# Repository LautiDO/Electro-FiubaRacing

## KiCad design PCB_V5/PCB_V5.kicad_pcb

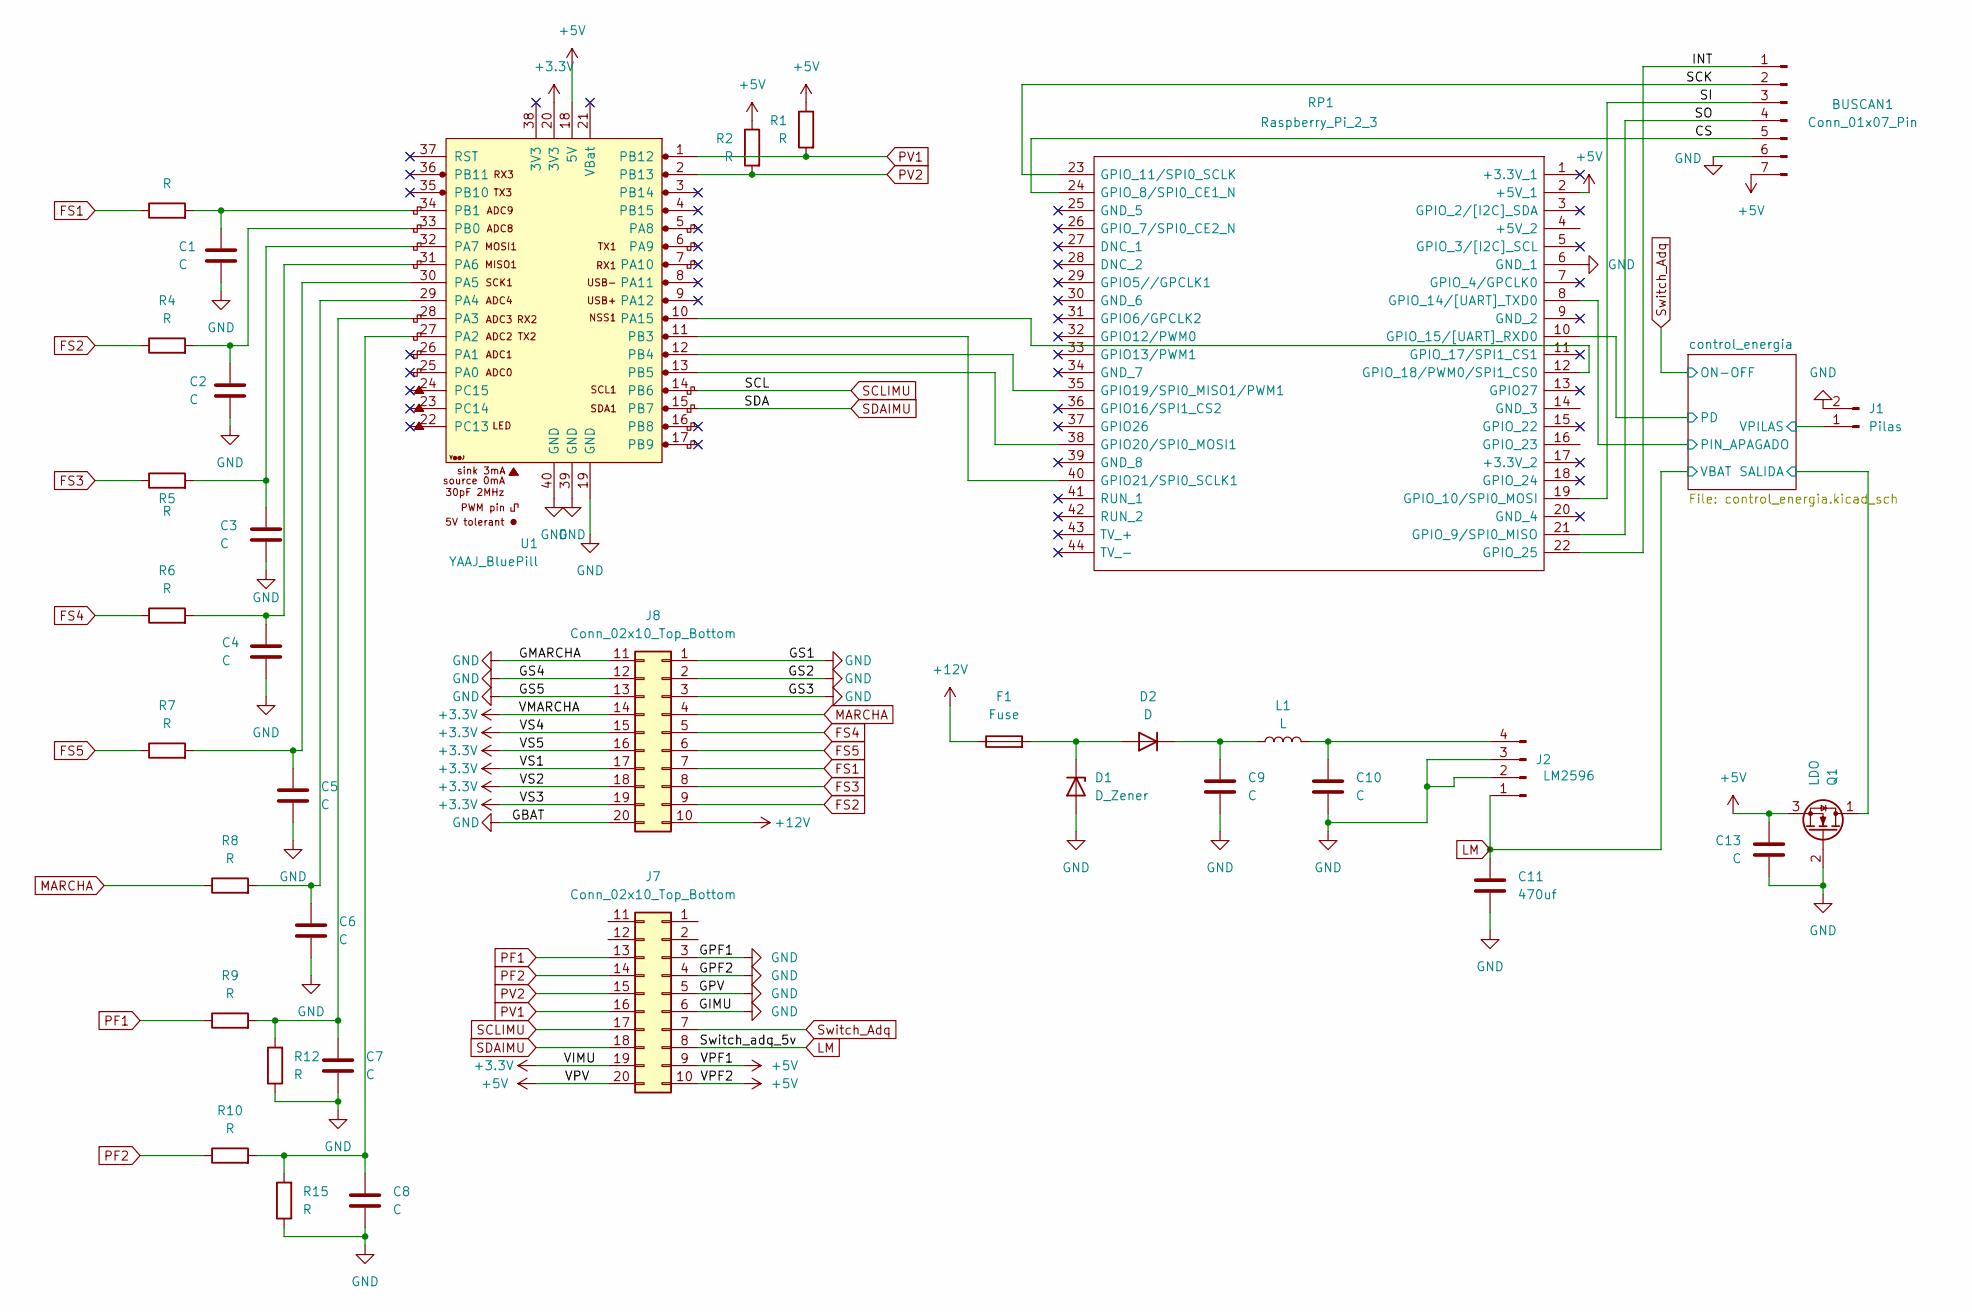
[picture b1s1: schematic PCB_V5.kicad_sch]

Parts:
BUSCAN1: Conn_01x07_Pin; PinHeader_1x07_P2.54mm_Vertical
C1, C2, C3, C4, C5, C6, C7, C8, C9, C10, C13: C; CP_Radial_D5.0mm_P2.50mm
C11: 470uf; CP_Radial_D5.0mm_P2.50mm
D1: D_Zener; D_DO-201_P15.24mm_Horizontal
D2: D; D_DO-201_P15.24mm_Horizontal
F1: Fuse; Fuseholder_Cylinder-5x20mm_Schurter_0031_8201_Horizontal_Op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
J1: Pilas; TerminalBlock_Phoenix_PT-1,5-2-5.0-H_1x02_P5.00mm_Horizontal
J2: LM2596; PinHeader_1x04_P2.54mm_Vertical
J7, J8: Conn_02x10_Top_Bottom; Molex_Mini-Fit_Jr_5566-20A2_2x10_P4.20mm_Vertical
L1: L; Transformer_CHK_EI38-3VA_Neutral
Q1: LDO; TO-220-3_Vertical
R1, R2, R3, R4, R5, R6, R7, R8, R9, R10, R12, R15: R; R_Axial_DIN0207_L6.3mm_D2.5mm_P7.62mm_Horizontal
RP1: Raspberry_Pi_2_3; PinHeader_2x20_P2.54mm_Vertical; Manufacturer_Part_Number Raspberry Pi 2 or 3
U1: YAAJ_BluePill; PinHeader_2x20_P2.54mm_Vertical

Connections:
+3.3V: J7.19, J8.14, J8.15, J8.16, J8.17, J8.18, J8.19, U1.20 (3V3)
+5V: BUSCAN1.7, C13.1, J7.9, J7.10, J7.20, Q1.3 (S), R1.1, R2.1, RP1.2 (+5V_1), U1.18 (5V)
+12V: F1.1, J8.10
/CS: BUSCAN1.5, RP1.24 (GPIO_8/SPI0_CE1_N)
/INT: BUSCAN1.1, RP1.22 (GPIO_25)
/SCK: BUSCAN1.2, RP1.23 (GPIO_11/SPI0_SCLK)
/SI: BUSCAN1.3, RP1.19 (GPIO_10/SPI0_MOSI)
/SO: BUSCAN1.4, RP1.21 (GPIO_9/SPI0_MISO)
/control_energia/PD: RP1.10 (GPIO_15/[UART]_RXD0); also elsewhere on the board
/control_energia/PIN_APAGADO: RP1.8 (GPIO_14/[UART]_TXD0); also elsewhere on the board
/control_energia/SALIDA: Q1.1 (D); also elsewhere on the board
/control_energia/VPILAS: J1.1; also elsewhere on the board
FS1: J8.7, R3.1
FS2: J8.9, R4.1
FS3: J8.8, R5.1
FS4: J8.5, R6.1
FS5: J8.6, R7.1
GND: BUSCAN1.6, C1.2, C2.2, C3.2, C4.2, C5.2, C6.2, C7.2, C8.2, C9.2, C10.2, C11.2, C13.2, D1.2 (A), J1.2, J2.2, J2.3, J7.3, J7.4, J7.5, J7.6, J8.1, J8.2, J8.3, J8.11, J8.12, J8.13, J8.20, Q1.2 (G), R12.1, R15.1, RP1.6 (GND_1), U1.19 (GND), U1.39 (GND), U1.40 (GND); also elsewhere on the board
LM: C11.1, J2.1, J7.8; also elsewhere on the board
MARCHA: J8.4, R8.1
unnamed: D1.1 (K), D2.2 (A), F1.2
unnamed: C9.1, D2.1 (K), L1.1
unnamed: C10.1, J2.4, L1.2
unnamed: RP1.35 (GPIO19/SPI0_MISO1/PWM1), U1.12 (PB4)
unnamed: RP1.38 (GPIO20/SPI0_MOSI1), U1.13 (PB5)
unnamed: RP1.40 (GPIO21/SPI0_SCLK1), U1.11 (PB3)
unnamed: RP1.12 (GPIO_18/PWM0/SPI1_CS0), U1.10 (PA15)
unnamed: C8.1, R10.2, R15.2, U1.27 (PA2)
unnamed: C7.1, R9.2, R12.2, U1.28 (PA3)
unnamed: C6.1, R8.2, U1.29 (PA4)
unnamed: C5.1, R7.2, U1.30 (PA5)
unnamed: C4.1, R6.2, U1.31 (PA6)
unnamed: C3.1, R5.2, U1.32 (PA7)
unnamed: C2.1, R4.2, U1.33 (PB0)
unnamed: C1.1, R3.2, U1.34 (PB1)
PF1: J7.13, R9.1
PF2: J7.14, R10.1
PV1: J7.16, R1.2, U1.1 (PB12)
PV2: J7.15, R2.2, U1.2 (PB13)
SCLIMU: J7.17, U1.14 (PB6)
SDAIMU: J7.18, U1.15 (PB7)
Switch_Adq: J7.7; also elsewhere on the board

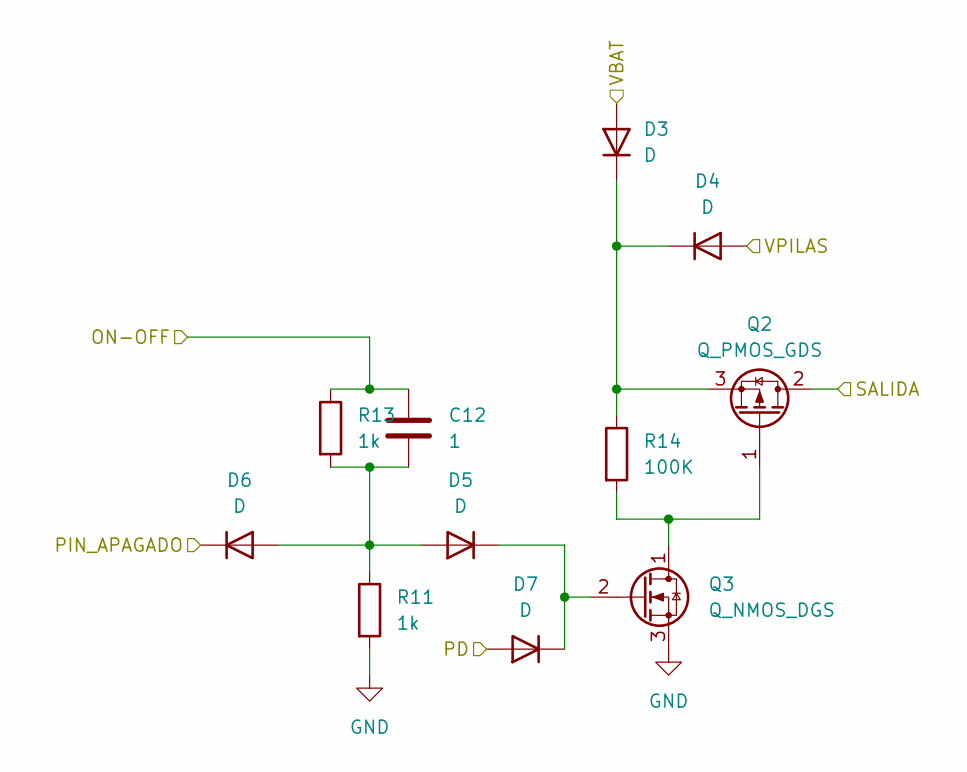
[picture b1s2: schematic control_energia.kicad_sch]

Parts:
C12: 1; CP_Radial_D5.0mm_P2.50mm
D3, D4, D5, D6, D7: D; R_Axial_DIN0207_L6.3mm_D2.5mm_P7.62mm_Horizontal
Q2: Q_PMOS_GDS; TO-220-3_Vertical
Q3: Q_NMOS_DGS; TO-92_HandSolder
R11, R13: 1k; R_Axial_DIN0207_L6.3mm_D2.5mm_P7.62mm_Horizontal
R14: 100K; R_Axial_DIN0207_L6.3mm_D2.5mm_P7.62mm_Horizontal

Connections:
/control_energia/PD: D7.2 (A); also elsewhere on the board
/control_energia/PIN_APAGADO: D6.1 (K); also elsewhere on the board
/control_energia/SALIDA: Q2.2 (D); also elsewhere on the board
/control_energia/VPILAS: D4.2 (A); also elsewhere on the board
GND: Q3.3 (S), R11.2; also elsewhere on the board
LM: D3.2 (A); also elsewhere on the board
unnamed: D3.1 (K), D4.1 (K), Q2.3 (S), R14.1
unnamed: C12.2, D5.2 (A), D6.2 (A), R11.1, R13.2
unnamed: D5.1 (K), D7.1 (K), Q3.2 (G)
unnamed: Q2.1 (G), Q3.1 (D), R14.2
Switch_Adq: C12.1, R13.1; also elsewhere on the board

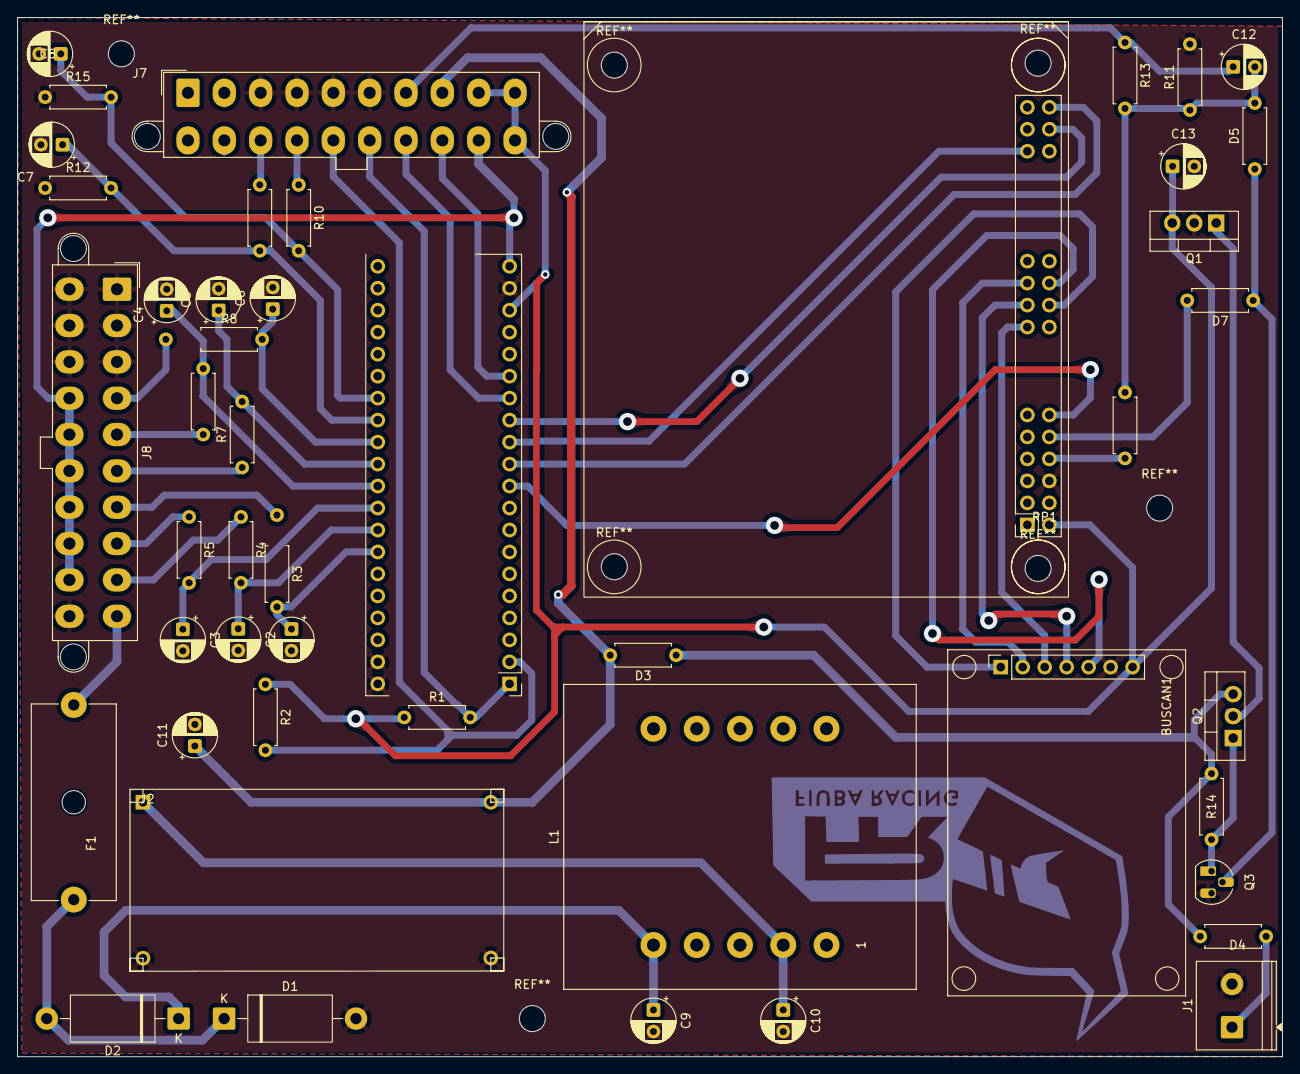
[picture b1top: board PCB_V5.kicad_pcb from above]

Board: 2 copper layers, 146.2 x 120.1 mm, 47 parts (0 on the bottom side), 46 nets.

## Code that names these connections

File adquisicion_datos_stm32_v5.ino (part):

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int t5      = 3860;   // Quinta
int t6      = 3700;   // Sexta
int neutro  = 4095;   // Neutro
int pin_cambios = PA4;
int tolerancia = 5;
int cambio = 0;

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const float DFIJO   =  0.0f;
const float K_ELAST = 35.0f;

const int PIN_EXT1 = PA6;
const int PIN_EXT2 = PA5;
const int PIN_EXT3 = PB1;
const int PIN_EXT4 = PA3;
const int PIN_EXT5 = PB0;


//====================================================
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//====================================================
//          ENCODER VOLANTE
//====================================================
const int PIN_ENCODER_A = PB12;
const int PIN_ENCODER_B = PB13;

volatile long pulsos         = 0;
         long pulsos_anterior = 0;
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//====================================================

int pin_presion1 = PA1;
int pin_presion2 = PA2;



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  rcc_clk_enable(RCC_GPIOB);
  rcc_clk_enable(RCC_AFIO); 

  // 2. Liberar pines JTAG (PA15, PB3, PB4) para que funcionen como SPI
  // Esto es CRÍTICO para que el micro no ignore estos pines
  afio_cfg_debug_ports(AFIO_DEBUG_SW_ONLY);

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  afio_remap(AFIO_REMAP_SPI1); 

  // 4. Configurar los NUEVOS pines según el Remap de SPI1
  // NSS: PA15 | SCK: PB3 | MISO: PB4 | MOSI: PB5
  gpio_set_mode(GPIOA, 15, GPIO_INPUT_FLOATING); 
  gpio_set_mode(GPIOB, 3, GPIO_INPUT_FLOATING);  
  gpio_set_mode(GPIOB, 5, GPIO_INPUT_FLOATING);  
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
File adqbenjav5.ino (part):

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int t5      = 3860;   // Quinta
int t6      = 3700;   // Sexta
int neutro  = 4095;   // Neutro
int pin_cambios = PA4;
int cambio = 0;

int estado_actual = -1;         // último cambio CONFIRMADO
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const float DFIJO   =   0.0f;
const float K_ELAST =  35.0f;

const int PIN_EXT1 = PA6;
const int PIN_EXT2 = PA5;
const int PIN_EXT3 = PB1;
const int PIN_EXT4 = PA3;
const int PIN_EXT5 = PB0;

//====================================================
//                      IMU
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//====================================================
//          ENCODER VOLANTE
//====================================================
const int PIN_ENCODER_A = PB12;
const int PIN_ENCODER_B = PB13;

volatile long pulsos         = 0;
         long pulsos_anterior = 0;
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//====================================================
//                      PRESIONES
//====================================================
int pin_presion1 = PA3;
int pin_presion2 = PA2;

//====================================================
//                      SETUP
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  afio_cfg_debug_ports(AFIO_DEBUG_SW_ONLY);
  afio_remap(AFIO_REMAP_SPI1); 

  pinMode(PA15, INPUT_PULLUP);
  attachInterrupt(digitalPinToInterrupt(PA15), nss_rising_isr, RISING);

  gpio_set_mode(GPIOA, 15, GPIO_INPUT_FLOATING); 
  gpio_set_mode(GPIOB, 3, GPIO_INPUT_FLOATING);  
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  nvic_irq_enable(NVIC_SPI1);
}
//====================================================
//         ISR — CHIP SELECT (PA15 / NSS)
//====================================================
void nss_rising_isr() {
  // Cuando la Raspi levanta CS a 3.3V, la transferencia terminó.
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//====================================================
//         RECUPERACIÓN DE BUS I2C
//====================================================
#define I2C_RECOVERY_SCL PB6
#define I2C_RECOVERY_SDA PB7

void recuperarBusI2C() {
  pinMode(I2C_RECOVERY_SDA, INPUT_PULLUP);
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
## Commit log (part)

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2025-07-19 Add codigos de prueba rapido, wide band
2025-07-24 verision1
2025-07-24 version2
2025-07-26 Codigo memoria funcionando
2025-08-11 Guardado de Memoria OK
2025-08-18 Create lll
2025-08-18 Create ll
2025-08-28 create gps prueba
2025-09-08 codigo Gps funcionando
2025-09-09 Subo el simulador de los sensores del motor, y el emulador de puerto usb para transmisión de datos continuos
2025-09-16 cambios menores a funcionamiento del sensor del aire
2025-09-16 Añadir funcionalidad de windows
2025-09-16 README y documentación para Linux
2025-09-16 Agregar documentación para Windows
2025-09-18 Implementación del resto de sensores, y funcionamiento de velocidad.
2025-09-18 Funcionamiento del resto de sensores, excepto F.suspension
2025-09-19 Create nose
2025-09-29 Adaptado a MacOS
2025-10-03 Cambio de formato en cada sensor
2025-10-10 modificado con boton el guardado de memoria
2025-10-16 modificado con la temperatura del motor
2025-11-07 andan temp motor, tps y mas o menos temp aire
2025-11-20 utlima version
2025-11-21 Update Purbe blue pill
    El codigo se dietiene si no detrecta la memoria
2025-12-11 codigo que lee rpm bien
2026-01-12 codigo que guarda en memoria, mide extensometros, mide rpm
2026-01-12 codigo extensometros
2026-01-12 codigo imu
2026-02-03 Codigo encoder que anda, optico
2026-02-03 para sacar los datos del motor en la ecu
2026-02-03 version final
2026-03-06 slave parte stm
2026-03-07 Create master-slave
2026-03-18 codigo con todo unido
2026-03-26 master-slave
2026-03-27 agrega la parte de sincronizar si se corre
2026-03-27 anda bien como slave, pero no soluciona lo de la imu
2026-04-02 codigo anda casa lauti 2/4
2026-04-02 Comunicacion Can
2026-04-09 test_spi_raspi
    Prueba de la comunicaciones spi RASPI funcinando ok
2026-04-16 cableado lauti
2026-04-23 gp anda v2
2026-04-24 Nueva version v1.0
    Sript mejorado para la comunicacion CAN con la pantalla
2026-04-24 Config del CAN bus
2026-04-24 Create Pruebas Ecu-Raspy
2026-04-24 Rename Pruebas Ecu-Raspy to ELIMINAR
2026-04-24 Toturiales Raspi
2026-04-25 Repositorio ordenado
2026-04-25 Integracion de bus CAN con los datos de la ECU
    Comunicaion CAN funcionando desde la Raspi
2026-04-27 add config
2026-05-07 Codigo Expo Fiuba
2026-05-08 Codigo de los cambios que funciona con arduino y motor
2026-05-14 pcb version final con logo
2026-05-15 pcb que le mandamos al lci
2026-05-15 se agrego la funcion de los cambios
2026-05-15 Pantalla andando con valores cambiados de escalam
2026-05-17 v4 con las correcciones de lci
2026-05-21 se agrego la funcion de medir presion
2026-05-22 se agrego la medicion de la presion y de los cambios
2026-05-22 v4 de telemetria unificada, falta poner bateria
2026-06-30 Ord Repo
